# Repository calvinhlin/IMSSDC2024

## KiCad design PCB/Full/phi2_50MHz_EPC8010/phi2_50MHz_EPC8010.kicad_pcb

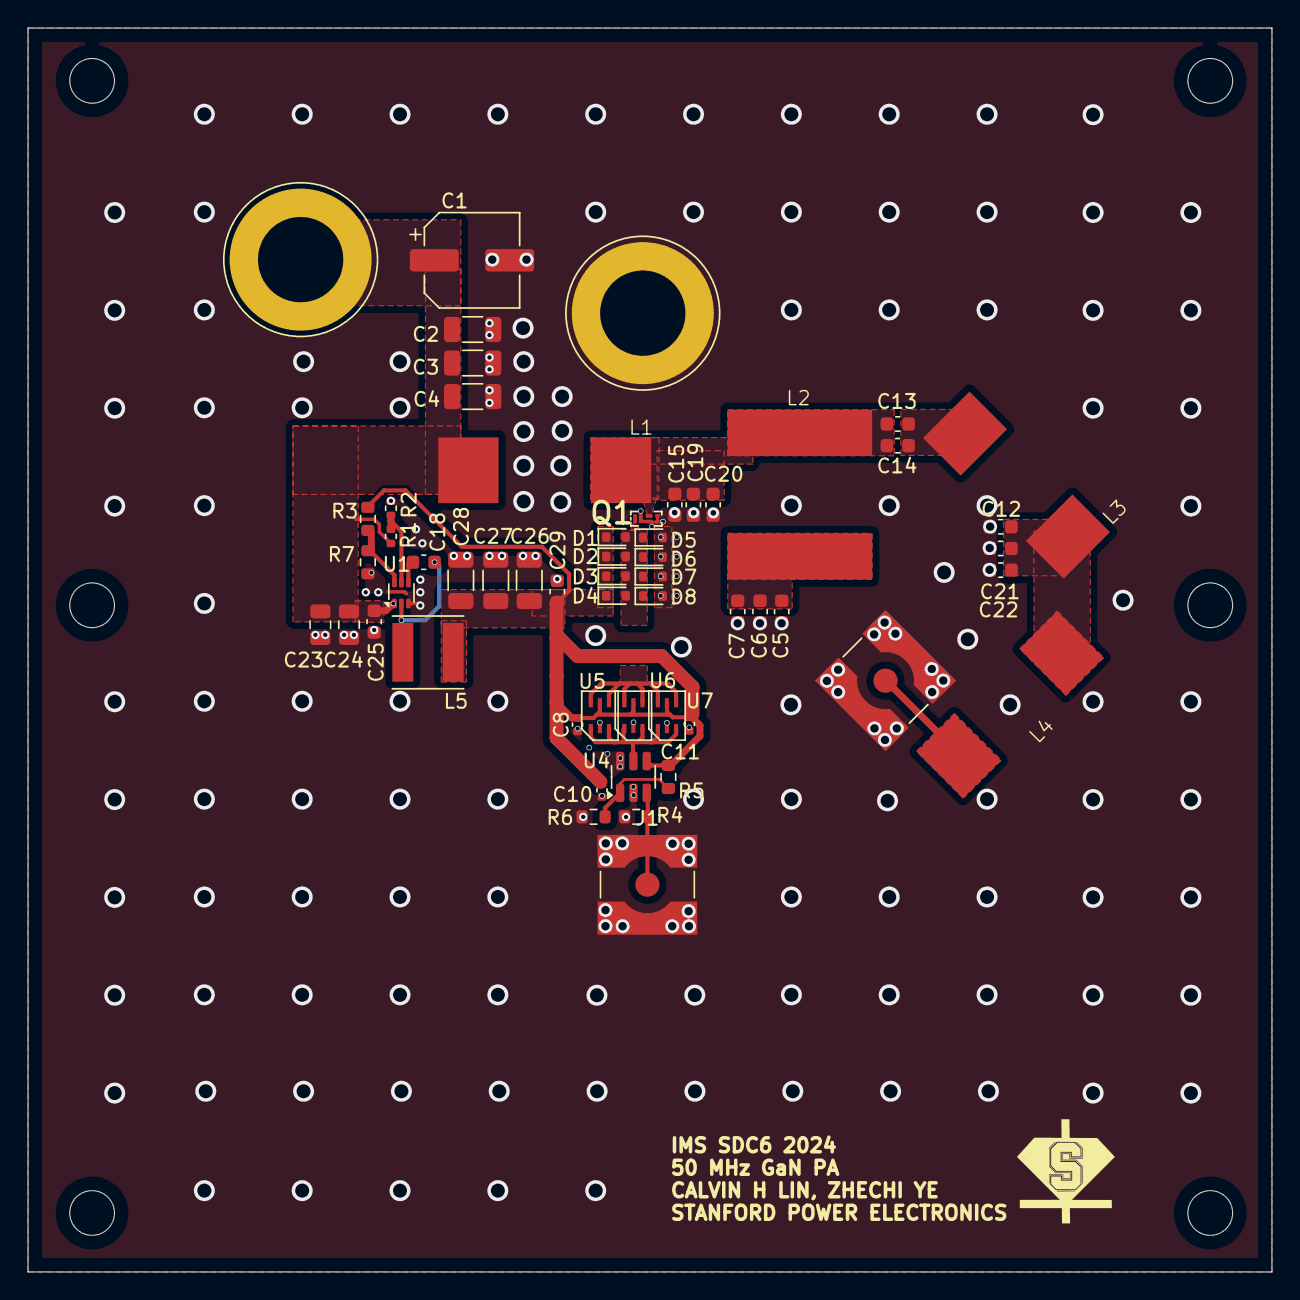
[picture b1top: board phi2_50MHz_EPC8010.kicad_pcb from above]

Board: 2 copper layers, 89.0 x 89.0 mm, 56 parts (0 on the bottom side), 17 nets.

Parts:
C1: C_Small; CP_Elec_6.3x7.7
C2, C3, C4: C_Small; C_1206_3216Metric
C5, C6, C7, C12, C13, C14, C15, C19, C20, C21, C22: C; C_0603_1608Metric
C8, C11: C; C_0402_1005Metric
C10: C_Small; C_0402_1005Metric
C18: 0.1u; C_0603_1608Metric
C23, C24: 10u; C_0805_2012Metric
C25, C29: 100n; C_0603_1608Metric
C26, C27, C28: 22u; C_1206_3216Metric
D1, D2, D3, D4, D5, D6, D7, D8: SMS3922; D_SOD-523
J1: RF_IN; SMA_Amphenol_132134-10_Vertical
J2: RF_OUT; SMA_Amphenol_132134-10_Vertical
J5, J6: Conn_01x01_Pin; Banana_Jack_1Pin
L1: 25n; L_Coilcraft_ZA9423
L2: 18n; Coilcraft_1212VS
L3: 81n; Coilcraft_2014VS
L4: 133n; Coilcraft_2014VS
L5: 4.7u; L_Taiyo-Yuden_MD-5050
Q1: EPC8010; D0221
R1: 100k; R_0402_1005Metric
R2: 15k; R_0402_1005Metric
R3: 220k; R_0603_1608Metric
R4: 50; R_0603_1608Metric
R5: OPEN; R_0603_1608Metric
R6: SHORT; R_0603_1608Metric
R7: 30k; R_0603_1608Metric
U1: TPS563203; SOT-563
U4: TLV3501; SOT-23-6
U5, U6, U7: NC7WZ16; nc7wz04_sc-88_SOIC-6

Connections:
+5V: C8.2, C10.1, C11.2, C26.1, C27.1, C28.1, C29.1, D1.1 (K), D2.1 (K), D3.1 (K), D4.1 (K), L5.2, R3.1, R5.1, U4.4 (V+), U5.5 (VCC), U6.5 (VCC), U7.5 (VCC)
+12V: C1.1, C2.1, C3.1, C4.1, C23.1, C24.1, C25.1, J5.1, L1.1, R1.1, U1.1 (VIN)
/D: C13.1, C14.1, C15.1, C19.1, C20.1, L1.2, L2.1, Q1.4 (D)
/G: D1.2 (A), D2.2 (A), D3.2 (A), D4.2 (A), D5.1 (K), D6.1 (K), D7.1 (K), D8.1 (K), Q1.1 (G)
/G1: U5.4 (Y2), U5.6 (Y1), U6.4 (Y2), U6.6 (Y1), U7.4 (Y2), U7.6 (Y1)
/RF_IN: J1.1 (In), R4.2, U4.3 (+IN)
/RF_OUT: J2.1 (In), L4.2
GND: C1.2, C2.2, C3.2, C4.2, C5.2, C6.2, C7.2, C8.1, C10.2, C11.1, C12.2, C15.2, C19.2, C20.2, C21.2, C22.2, C23.2, C24.2, C25.2, C26.2, C27.2, C28.2, C29.2, D5.2 (A), D6.2 (A), D7.2 (A), D8.2 (A), J1.2 (Ext), J2.2 (Ext), J6.1, Q1.2 (SG), Q1.3 (SP1), Q1.5 (SP2), Q1.6 (Sub), R2.2, R4.1, R6.2, R7.2, U1.3 (GND), U4.2 (V-), U4.6 (SHDN), U5.2 (GND), U6.2 (GND), U7.2 (GND)
unnamed: C5.1, C6.1, C7.1, L2.2
unnamed: C12.1, C21.1, C22.1, L3.2, L4.1
unnamed: C13.2, C14.2, L3.1
unnamed: C18.2, U1.4 (BST)
unnamed: R1.2, R2.1, U1.5 (EN)
unnamed: R3.2, R7.1, U1.6 (FB)
unnamed: C18.1, L5.1, U1.2 (SW)
unnamed: R5.2, R6.1, U4.1 (-IN)
unnamed: U4.5 (OUT), U5.1 (A1), U5.3 (A2), U6.1 (A1), U6.3 (A2), U7.1 (A1), U7.3 (A2)

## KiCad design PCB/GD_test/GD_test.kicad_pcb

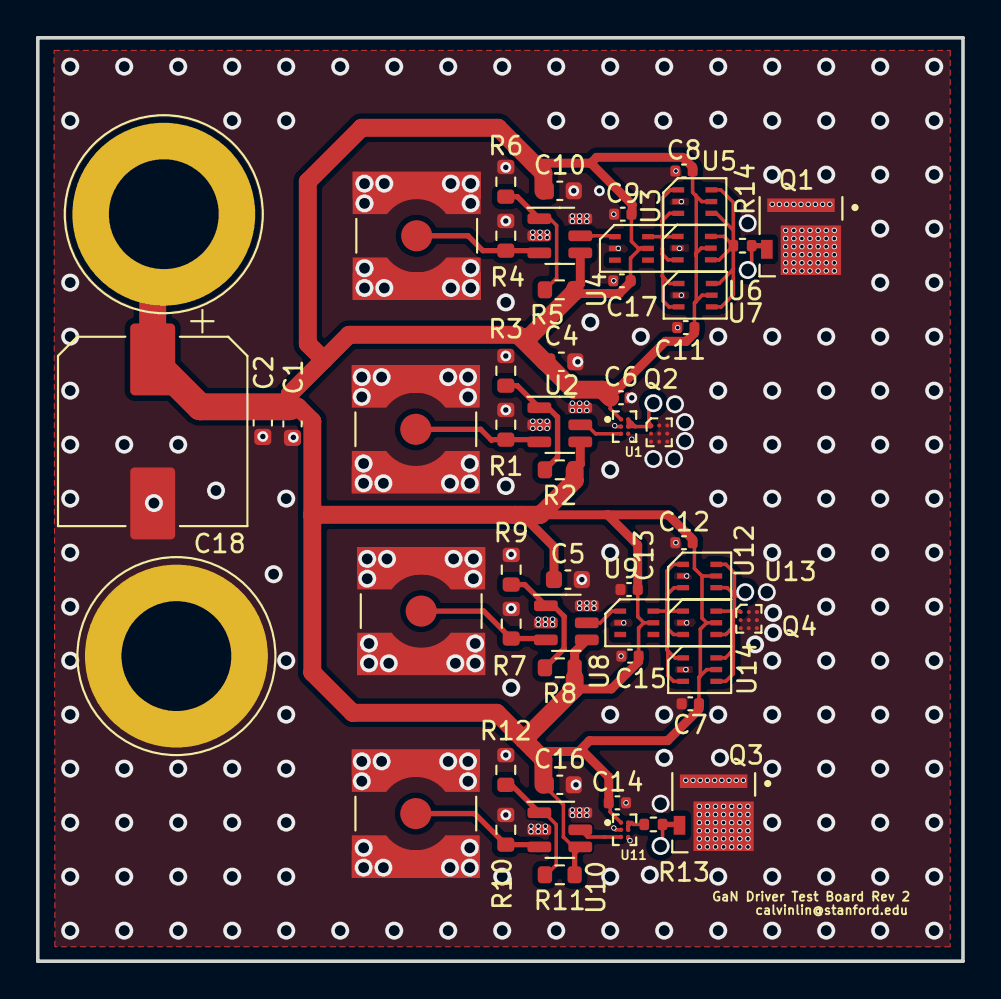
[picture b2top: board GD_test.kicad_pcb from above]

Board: 2 copper layers, 51.4 x 51.3 mm, 55 parts (0 on the bottom side), 22 nets.

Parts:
C1, C2, C4, C5, C10, C16: C_Small; C_0603_1608Metric
C6, C7, C8, C9, C11, C12, C13, C14, C15, C17: C_Small; C_0402_1005Metric
C18: C_Small; CP_Elec_10x10
J1, J2, J3, J4: RF_IN; SMA_Amphenol_132134-10_Vertical
J5, J6: Conn_01x01_Pin; Banana_Jack_1Pin
Q1, Q3: GS61004B-MR; TRANS_GS61004B-MR
Q2, Q4: EPC2214; BGA-9_3x3_6.0x6.0mm
R1, R4, R7, R10: 50; R_0603_1608Metric
R2, R5, R8, R11: OPEN; R_0603_1608Metric
R3, R6, R9, R12: SHORT; R_0603_1608Metric
R13, R14: 1; R_0402_1005Metric
U1, U11: LMG1020YFF; BGA6N40P3X2_125X85X62N
U2, U4, U8, U10: TLV3501; SOT-23-6
U3, U5, U6, U7, U9, U12, U13, U14: NC7WZ04; nc7wz04_sc-88_SOIC-6

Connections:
+5V: C1.1, C2.1, C4.1, C5.1, C6.1, C7.1, C8.2, C9.2, C10.1, C11.2, C12.2, C13.2, C14.1, C15.2, C16.1, C17.1, C18.1, J5.1, R2.1, R5.1, R8.1, R11.1, U1.A1 (V_{DD}), U2.4 (V+), U3.5 (VCC), U4.4 (V+), U5.5 (VCC), U6.5 (VCC), U7.5 (VCC), U8.4 (V+), U9.5 (VCC), U10.4 (V+), U11.A1 (V_{DD}), U12.5 (VCC), U13.5 (VCC), U14.5 (VCC)
/RF_IN_1: J1.1 (In), R1.2, U2.3 (+IN)
/RF_IN_2: J4.1 (In), R4.2, U4.3 (+IN)
/RF_IN_3: J2.1 (In), R7.2, U8.3 (+IN)
/RF_IN_4: J3.1 (In), R10.2, U10.3 (+IN)
/inv_out: U9.6 (Y1), U12.1 (A1), U12.3 (A2), U13.1 (A1), U13.3 (A2), U14.1 (A1), U14.3 (A2)
GND: C1.2, C2.2, C4.2, C5.2, C6.2, C7.2, C8.1, C9.1, C10.2, C11.1, C12.1, C13.1, C14.2, C15.1, C16.2, C17.2, C18.2, J1.2 (Ext), J2.2 (Ext), J3.2 (Ext), J4.2 (Ext), J6.1, Q1.1, Q1.3, Q2.2 (S), Q2.3 (S), Q2.4 (D), Q2.5 (D), Q2.6 (D), Q2.7 (D), Q2.8 (S), Q2.9 (S), Q3.1, Q3.3, Q4.2 (S), Q4.3 (S), Q4.4 (D), Q4.5 (D), Q4.6 (D), Q4.7 (D), Q4.8 (S), Q4.9 (S), R1.1, R3.2, R4.1, R6.2, R7.1, R9.2, R10.1, R12.2, U1.B1 (GND), U1.C2 (IN-), U2.2 (V-), U2.6 (SHDN), U3.2 (GND), U4.2 (V-), U4.6 (SHDN), U5.2 (GND), U6.2 (GND), U7.2 (GND), U8.2 (V-), U8.6 (SHDN), U9.2 (GND), U10.2 (V-), U10.6 (SHDN), U11.B1 (GND), U11.C2 (IN-), U12.2 (GND), U13.2 (GND), U14.2 (GND)
unnamed: Q1.2, R14.2
unnamed: Q2.1 (G), U1.A2 (OUTH), U1.B2 (OUTL)
unnamed: Q3.2, R13.2
unnamed: Q4.1 (G), U12.4 (Y2), U12.6 (Y1), U13.4 (Y2), U13.6 (Y1), U14.4 (Y2), U14.6 (Y1)
unnamed: U1.C1 (IN+), U2.5 (OUT)
unnamed: R2.2, R3.1, U2.1 (-IN)
unnamed: U3.1 (A1), U4.5 (OUT)
unnamed: U3.6 (Y1), U5.1 (A1), U5.3 (A2), U6.1 (A1), U6.3 (A2), U7.1 (A1), U7.3 (A2)
unnamed: R5.2, R6.1, U4.1 (-IN)
unnamed: R14.1, U5.4 (Y2), U5.6 (Y1), U6.4 (Y2), U6.6 (Y1), U7.4 (Y2), U7.6 (Y1)
unnamed: R8.2, R9.1, U8.1 (-IN)
unnamed: U8.5 (OUT), U9.1 (A1)
unnamed: R11.2, R12.1, U10.1 (-IN)
unnamed: U10.5 (OUT), U11.C1 (IN+)
unnamed: R13.1, U11.A2 (OUTH), U11.B2 (OUTL)

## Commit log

2024-02-17 imssdc 2024 first commit
2024-02-20 gate driver board
2024-02-20 gate driver gerbers and some extra changes
2024-02-21 gate driver stuff
2024-02-21 gate driver test board changes
2024-02-23 phi 2 design
2024-02-24 50 MHz design
2024-03-07 gate driver testboard rev 3 stuff
2024-03-11 gate driver rev 3 updates
2024-03-12 50 MHz stuff
2024-03-13 gate driver test board rev 2 gerbers commit
2024-04-03 some progress on 50 MHz design
2024-04-04 small schem progress
2024-04-07 mostly finalized schematic stuff for student design board
2024-04-09 rough draft of phi 2 board
2024-04-09 deleted some vias
2024-04-10 gerbers and rev1 board sent out
2024-04-10 added width to drain trace, now sent out board
2024-04-12 idk what i changed here
2024-04-17 kicad changes if i ever make a new board
2024-04-18 asdf
2024-04-24 matching network changes to ims design
2024-04-27 ims changes
2024-04-30 xcircuit stuff
2024-05-02 added report
2024-05-03 experimental data
2024-05-03 first report added
2024-05-06 gd test
2024-05-06 layout and gerbers with new epc device
2024-05-08 epc 8010 new board gerbers
2024-05-22 added a GS part just to test
2024-05-23 idk what this change is
2024-05-31 added measurement data
2024-06-06 checking output network
2024-09-06 lots of figures for magazine paper
2024-09-06 figures for microwave paper
2024-09-06 figure
2024-09-06 more figures
2024-09-10 a lot of figures stuff
2024-09-12 added bib file
2024-11-08 final push... project over
